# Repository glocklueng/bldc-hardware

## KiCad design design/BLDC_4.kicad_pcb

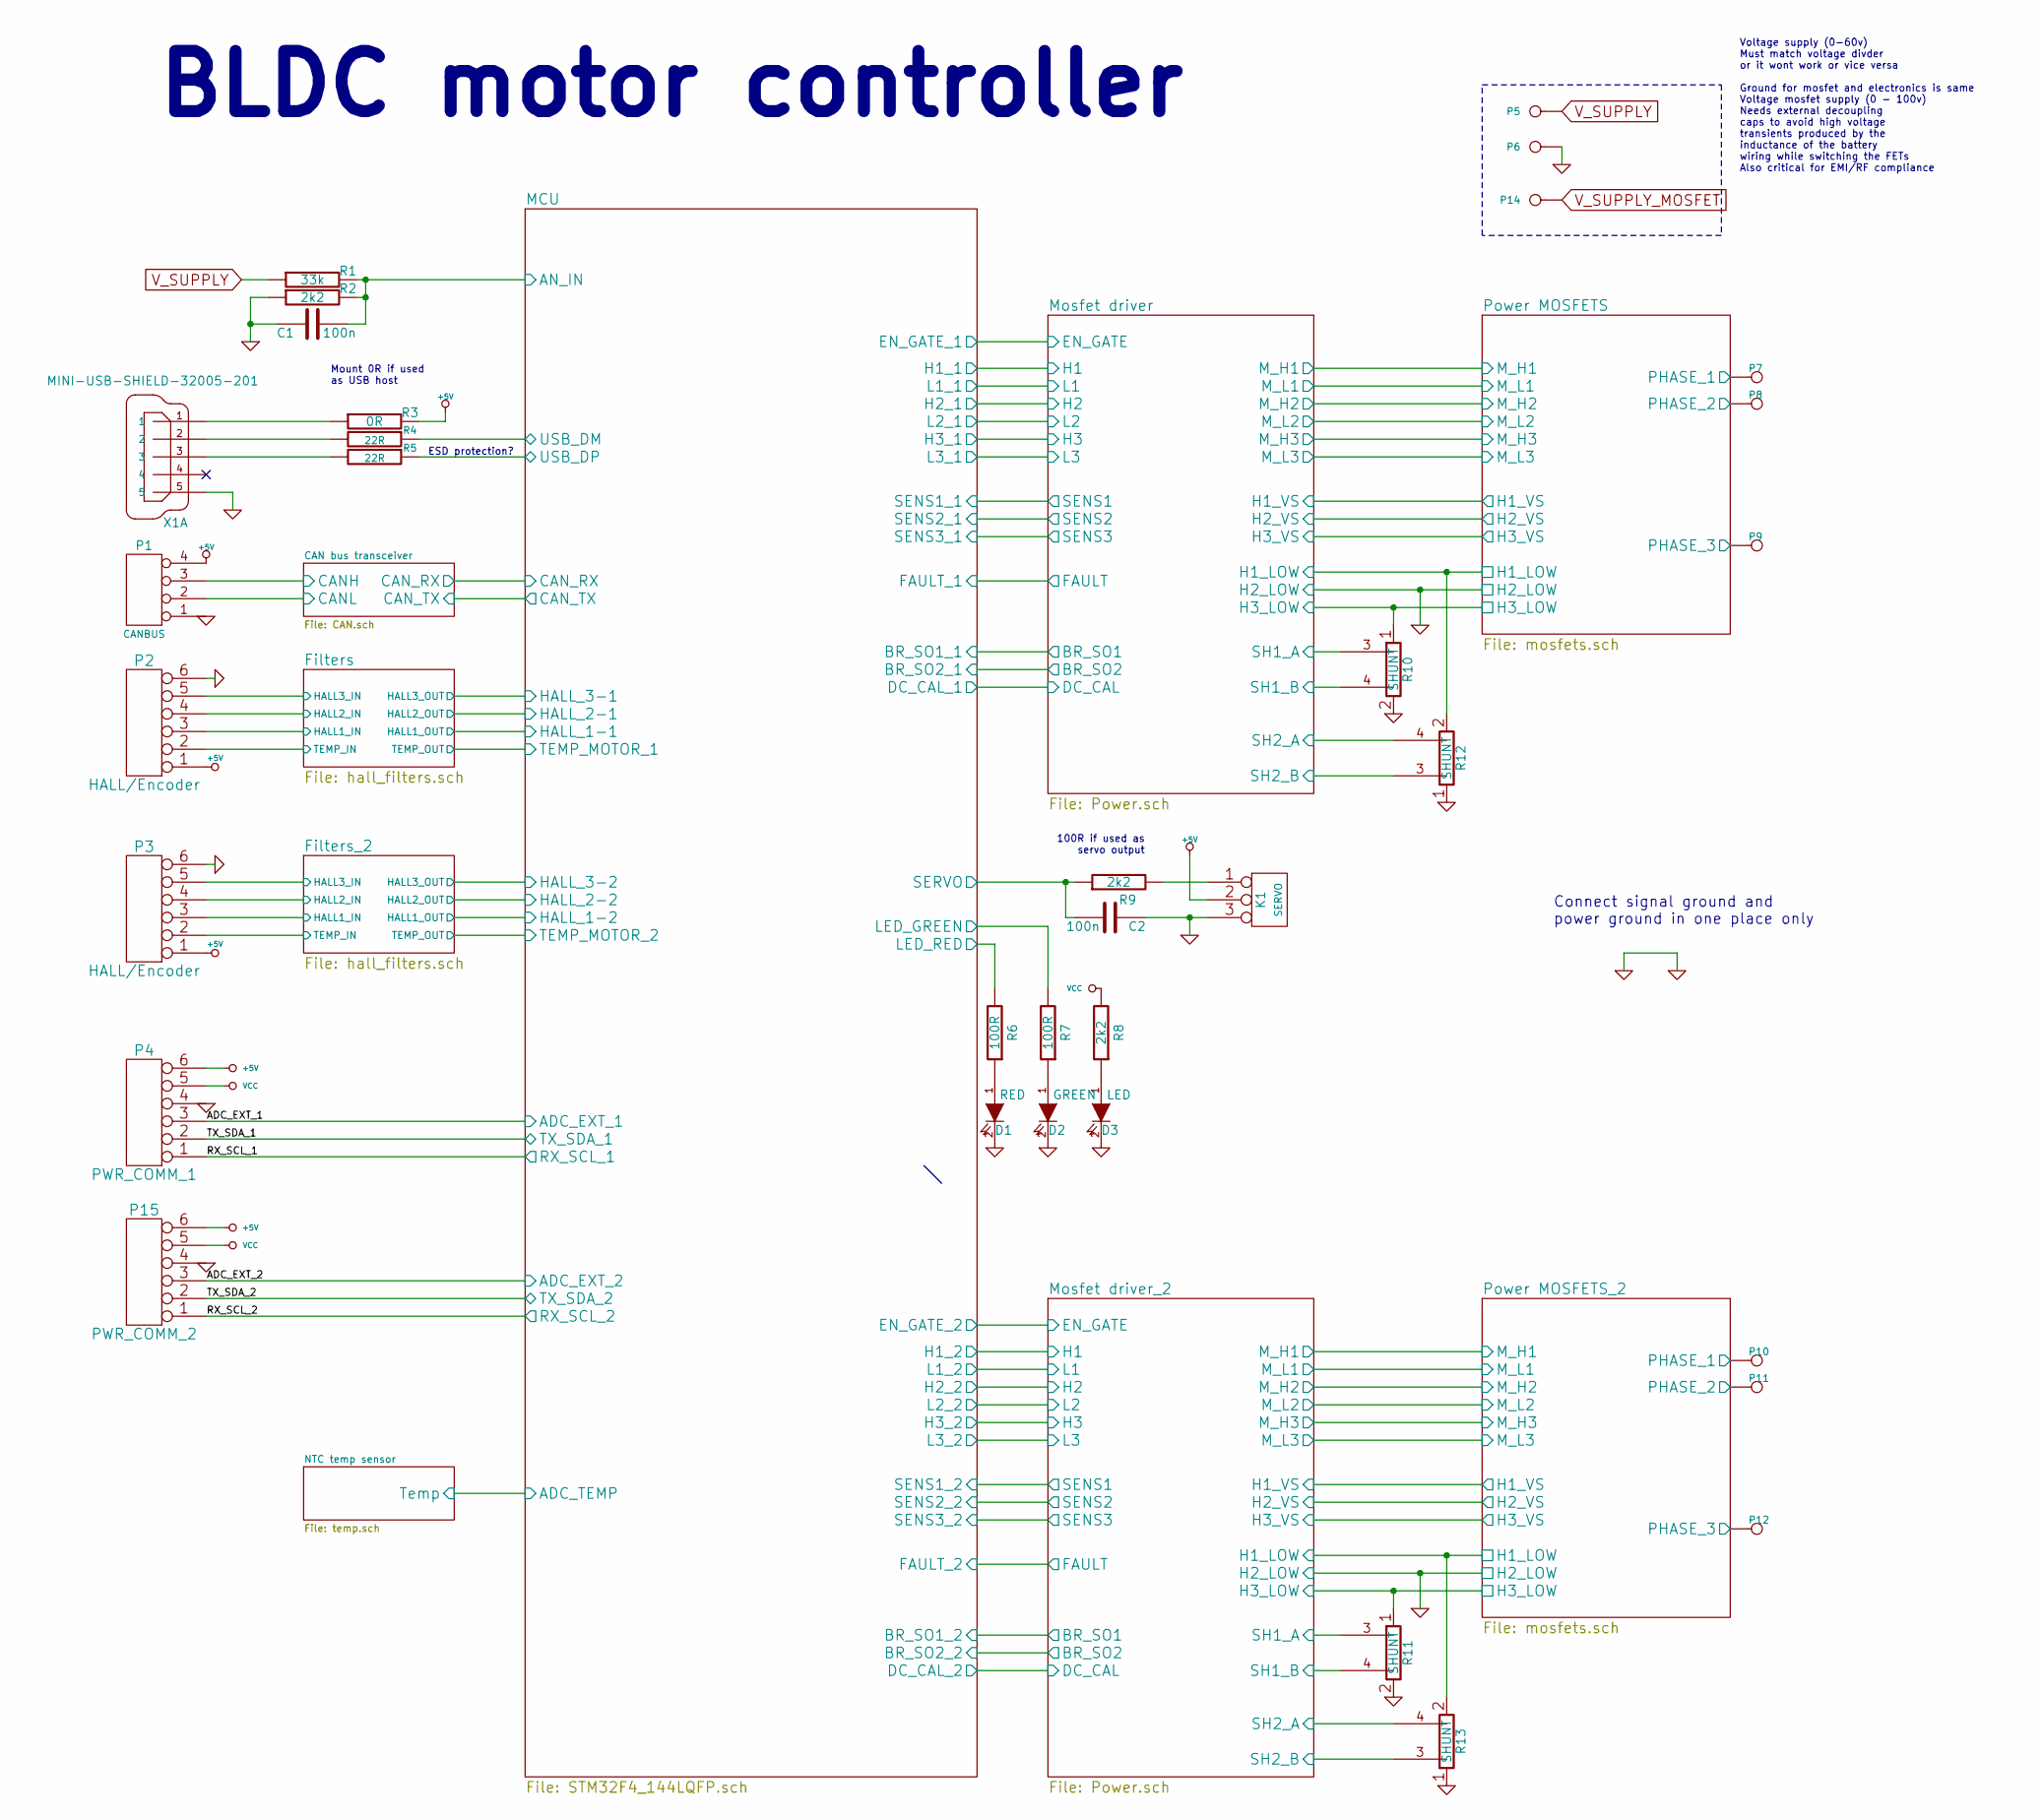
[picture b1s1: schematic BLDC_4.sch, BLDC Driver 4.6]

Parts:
C1, C2: 100n; SMD-0603_c
D1: RED; LED-0603
D2: GREEN; LED-0603
D3: LED; LED-0603
K1: SERVO; pinhead-1X03
P1: CANBUS; pinhead-1X04
P2, P3: HALL/Encoder; MICRO_JST_6
P4: PWR_COMM_1; MICRO_JST_6
P5, P14: IN+; 1PAD_4x5mm
P6: IN-; 1PAD_4x5mm
P7, P10: MOTOR3; 1PAD_4x5mm
P8, P11: MOTOR2; 1PAD_4x5mm
P9, P12: MOTOR1; 1PAD_4x5mm
P15: PWR_COMM_2; MICRO_JST_6
R1: 33k; SMD-0603_r
R2, R8, R9: 2k2; SMD-0603_r
R3: 0R; SMD-0603_r
R4, R5: 22R; SMD-0603_r
R6, R7: 100R; SMD-0603_r
R10, R11, R12, R13: SHUNT; WSLP2726
X1: MINI-USB-SHIELD-32005-201; con-cypressindustries-32005-201

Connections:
+5V: K1.2 (PM), P1.4, P2.1, P3.1, P4.6, P15.6, R3.2; also elsewhere on the board
/CAN bus transceiver/CANH: P1.3; also elsewhere on the board
/CAN bus transceiver/CANL: P1.2; also elsewhere on the board
/Filters/HALL1_IN: P2.3; also elsewhere on the board
/Filters/HALL2_IN: P2.4; also elsewhere on the board
/Filters/HALL3_IN: P2.5; also elsewhere on the board
/Filters/TEMP_IN: P2.2; also elsewhere on the board
/Filters_2/HALL1_IN: P3.3; also elsewhere on the board
/Filters_2/HALL2_IN: P3.4; also elsewhere on the board
/Filters_2/HALL3_IN: P3.5; also elsewhere on the board
/Filters_2/TEMP_IN: P3.2; also elsewhere on the board
/MCU/ADC_EXT_1: P4.3; also elsewhere on the board
/MCU/ADC_EXT_2: P15.3; also elsewhere on the board
/MCU/AN_IN: C1.2, R1.2, R2.2; also elsewhere on the board
/MCU/LED_GREEN: R7.2; also elsewhere on the board
/MCU/LED_RED: R6.2; also elsewhere on the board
/MCU/RX_SCL_1: P4.1; also elsewhere on the board
/MCU/RX_SCL_2: P15.1; also elsewhere on the board
/MCU/SERVO: C2.2, R9.1; also elsewhere on the board
/MCU/TX_SDA_1: P4.2; also elsewhere on the board
/MCU/TX_SDA_2: P15.2; also elsewhere on the board
/MCU/USB_DM: R4.1; also elsewhere on the board
/MCU/USB_DP: R5.1; also elsewhere on the board
/Mosfet driver/H3_VS: P9.1; also elsewhere on the board
/Mosfet driver/SH1_A: R10.3; also elsewhere on the board
/Mosfet driver/SH1_B: R10.4; also elsewhere on the board
/Mosfet driver/SH2_A: R12.4; also elsewhere on the board
/Mosfet driver/SH2_B: R12.3; also elsewhere on the board
/Mosfet driver_2/H3_VS: P12.1; also elsewhere on the board
/Mosfet driver_2/SH1_A: R11.3; also elsewhere on the board
/Mosfet driver_2/SH1_B: R11.4; also elsewhere on the board
/Mosfet driver_2/SH2_A: R13.4; also elsewhere on the board
/Mosfet driver_2/SH2_B: R13.3; also elsewhere on the board
GND: C1.1, C2.1, D1.2 (K), D2.2 (K), D3.2 (K), K1.3, P1.1, P2.6, P3.6, P4.4, P6.1, P15.4, R2.1, R10.2, R11.2, R12.1, R13.1, X1.5; also elsewhere on the board
unnamed: D1.1 (A), R6.1
unnamed: D2.1 (A), R7.1
unnamed: D3.1 (A), R8.1
unnamed: K1.1, R9.2
unnamed: R3.1, X1.1
unnamed: R4.2, X1.2
unnamed: R5.2, X1.3
VCC: P4.5, P15.5, R8.2; also elsewhere on the board
V_SUPPLY: P5.1, R1.1; also elsewhere on the board
V_SUPPLY_MOSFET: P14.1; also elsewhere on the board

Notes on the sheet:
100R if used as servo output
Mount 0R if used as USB host
ESD protection?
BLDC motor controller
Voltage mosfet supply (0 - 100v) Needs external decoupling caps to avoid high voltage transients produced by the inductance of the battery wiring while switching the FETs Also critical for EMI/RF compliance
Connect signal ground and power ground in one place only
Voltage supply (0-60v) Must match voltage divder or it wont work or vice versa Ground for mosfet and electronics is same

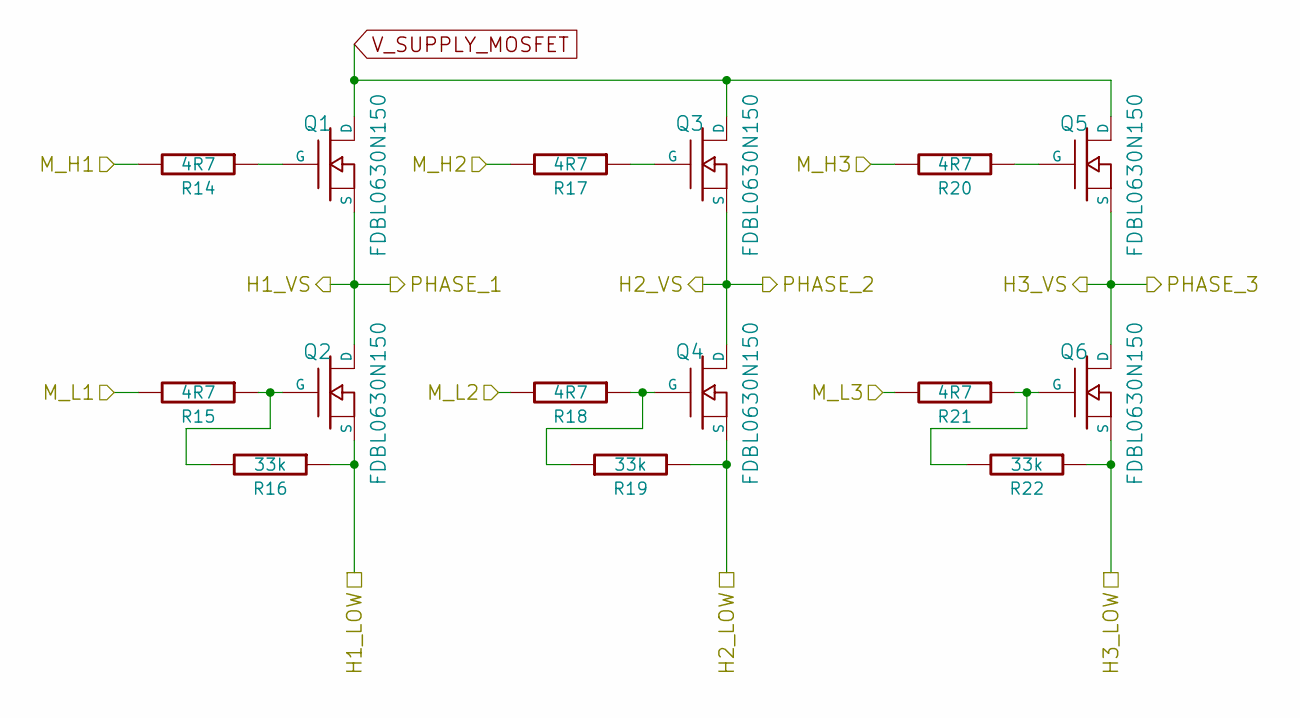
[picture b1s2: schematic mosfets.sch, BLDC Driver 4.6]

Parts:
Q2, Q3, Q5, Q6, Q7, Q10: FDBL0630N150; H-PSOF-8L
R59, R60, R62, R63, R65, R66: 4R7; SMD-0603_r
R61, R64, R67: 33k; SMD-0603_r

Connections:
/Mosfet driver/H3_VS: Q5.S, Q6.D; also elsewhere on the board
/Mosfet driver_2/M_H1: R59.2; also elsewhere on the board
/Mosfet driver_2/M_H2: R62.2; also elsewhere on the board
/Mosfet driver_2/M_H3: R65.2; also elsewhere on the board
/Mosfet driver_2/M_L1: R60.2; also elsewhere on the board
/Mosfet driver_2/M_L2: R63.2; also elsewhere on the board
/Mosfet driver_2/M_L3: R66.2; also elsewhere on the board
GND: Q10.S, R64.2; also elsewhere on the board
unnamed: Q7.G, R59.1
unnamed: Q10.G, R63.1, R64.1
V_SUPPLY_MOSFET: Q3.D, Q5.D, Q7.D; also elsewhere on the board

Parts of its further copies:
Q1, Q4, Q8, Q9, Q11, Q12: FDBL0630N150; H-PSOF-8L
R14, R15, R17, R18, R20, R21: 4R7; SMD-0603_r
R16, R19, R22: 33k; SMD-0603_r

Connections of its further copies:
/Mosfet driver/M_H1: R14.2; also elsewhere on the board
/Mosfet driver/M_H2: R17.2; also elsewhere on the board
/Mosfet driver/M_H3: R20.2; also elsewhere on the board
/Mosfet driver/M_L1: R15.2; also elsewhere on the board
/Mosfet driver/M_L2: R18.2; also elsewhere on the board
/Mosfet driver/M_L3: R21.2; also elsewhere on the board
/Mosfet driver_2/H3_VS: Q11.S, Q12.D; also elsewhere on the board
GND: Q4.S, R19.2; also elsewhere on the board
unnamed: Q1.G, R14.1
unnamed: Q4.G, R18.1, R19.1
V_SUPPLY_MOSFET: Q1.D, Q9.D, Q11.D; also elsewhere on the board

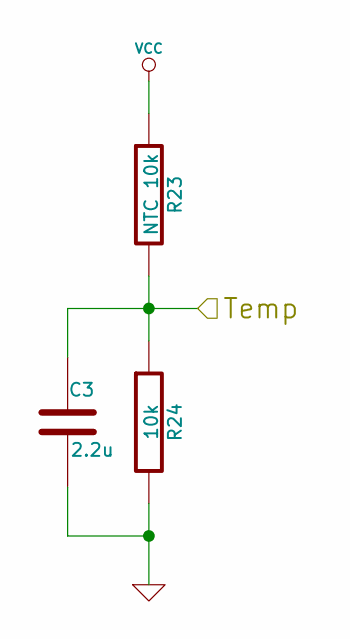
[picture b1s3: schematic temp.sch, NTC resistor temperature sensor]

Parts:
C3: 2.2u; SMD-0603_c
R23: NTC 10k; SMD-0603_r
R24: 10k; SMD-0603_r

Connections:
/MCU/ADC_TEMP: C3.1, R23.2, R24.1; also elsewhere on the board
GND: C3.2, R24.2; also elsewhere on the board
VCC: R23.1; also elsewhere on the board

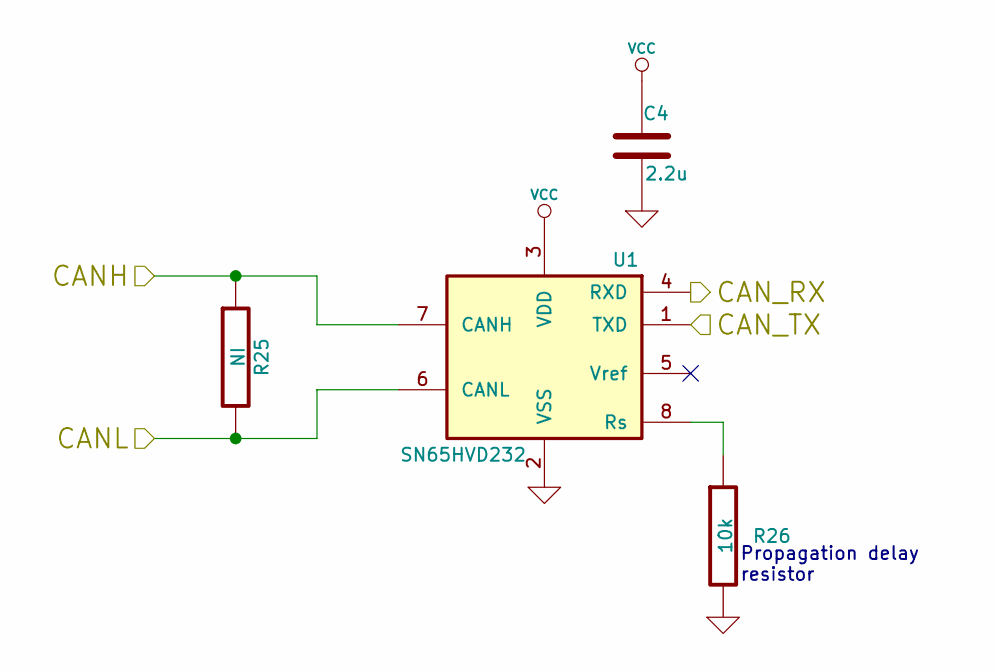
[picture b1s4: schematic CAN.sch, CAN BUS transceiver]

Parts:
C4: 2.2u; SMD-0402
R25: NI; SMD-0603_r
R26: 10k; SMD-0603_r
U1: SN65HVD232; SOIC-8-W

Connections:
/CAN bus transceiver/CANH: R25.1, U1.7 (CANH); also elsewhere on the board
/CAN bus transceiver/CANL: R25.2, U1.6 (CANL); also elsewhere on the board
/CAN bus transceiver/CAN_RX: U1.4 (RXD); also elsewhere on the board
/CAN bus transceiver/CAN_TX: U1.1 (TXD); also elsewhere on the board
GND: C4.2, R26.2, U1.2 (VSS); also elsewhere on the board
unnamed: R26.1, U1.8 (Rs)
VCC: C4.1, U1.3 (VDD); also elsewhere on the board

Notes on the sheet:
Propagation delay resistor

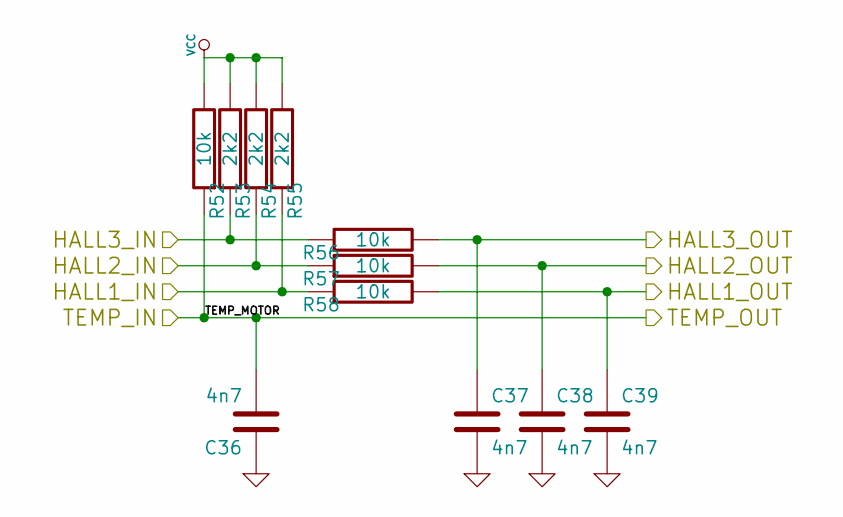
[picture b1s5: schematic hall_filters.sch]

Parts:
C5, C6, C7, C8: 4n7; SMD-0603_c
R27, R31, R32, R33: 10k; SMD-0603_r
R28, R29, R30: 2k2; SMD-0603_r

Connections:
/Filters/HALL1_IN: R30.1, R33.1; also elsewhere on the board
/Filters/HALL1_OUT: C8.1, R33.2; also elsewhere on the board
/Filters/HALL2_IN: R29.1, R32.1; also elsewhere on the board
/Filters/HALL2_OUT: C7.1, R32.2; also elsewhere on the board
/Filters/HALL3_IN: R28.1, R31.1; also elsewhere on the board
/Filters/HALL3_OUT: C6.1, R31.2; also elsewhere on the board
/Filters/TEMP_IN: C5.2, R27.1; also elsewhere on the board
GND: C5.1, C6.2, C7.2, C8.2; also elsewhere on the board
VCC: R27.2, R28.2, R29.2, R30.2; also elsewhere on the board

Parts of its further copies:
C36, C37, C38, C39: 4n7; SMD-0603_c
R52, R56, R57, R58: 10k; SMD-0603_r
R53, R54, R55: 2k2; SMD-0603_r

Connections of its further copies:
/Filters_2/HALL1_IN: R55.1, R58.1; also elsewhere on the board
/Filters_2/HALL1_OUT: C39.1, R58.2; also elsewhere on the board
/Filters_2/HALL2_IN: R54.1, R57.1; also elsewhere on the board
/Filters_2/HALL2_OUT: C38.1, R57.2; also elsewhere on the board
/Filters_2/HALL3_IN: R53.1, R56.1; also elsewhere on the board
/Filters_2/HALL3_OUT: C37.1, R56.2; also elsewhere on the board
/Filters_2/TEMP_IN: C36.2, R52.1; also elsewhere on the board
GND: C36.1, C37.2, C38.2, C39.2; also elsewhere on the board
VCC: R52.2, R53.2, R54.2, R55.2; also elsewhere on the board

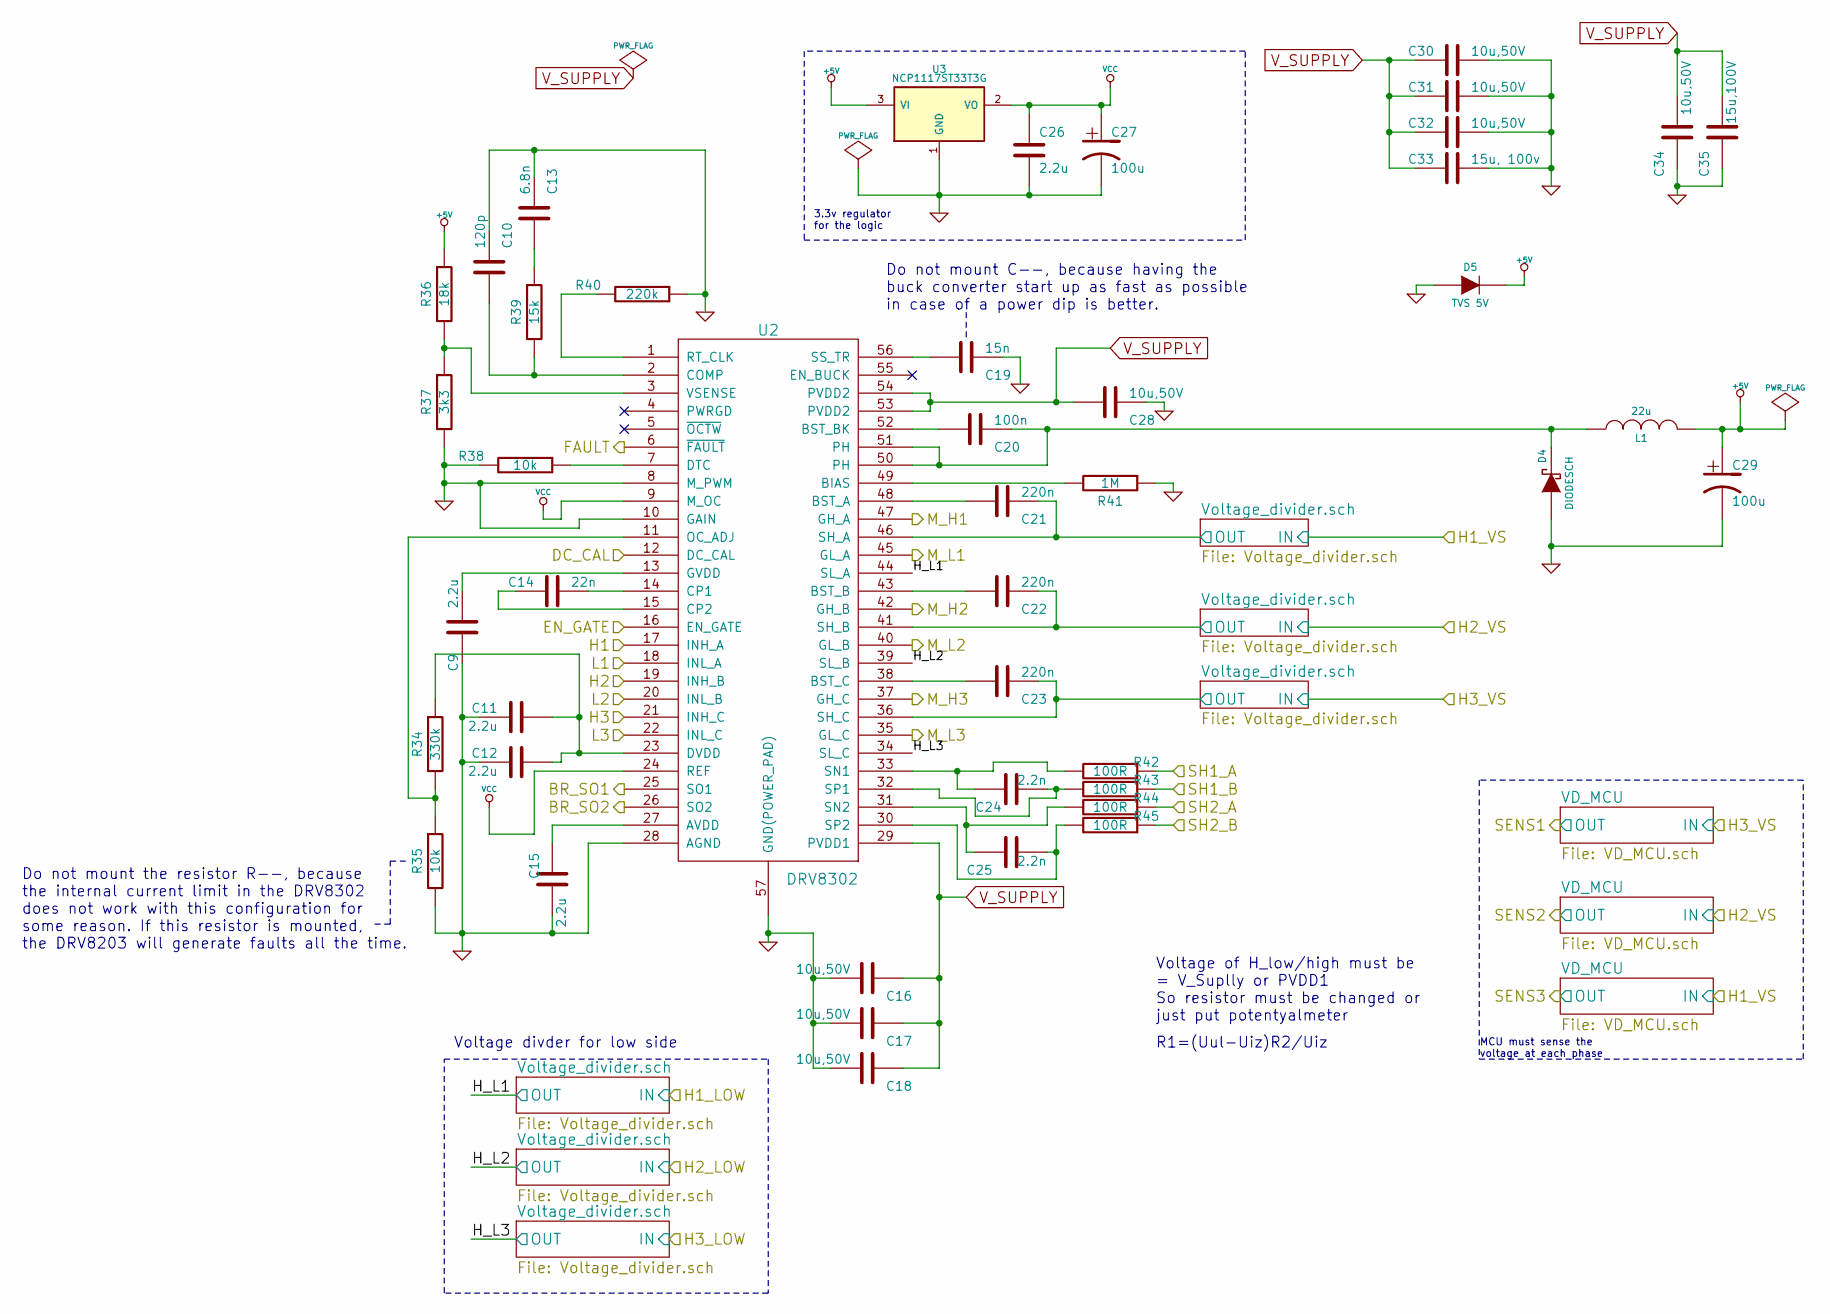
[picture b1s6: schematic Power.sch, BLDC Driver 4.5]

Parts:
C9, C15: 2.2u; SMD-0805
C10: 120p; SMD-0603_c
C11, C12, C26: 2.2u; SMD-0603_c
C13: 6.8n; SMD-0603_c
C14: 22n; SMD-0603_c
C16, C17, C18, C28, C30, C31, C32, C34: 10u,50V; SMD-1206
C19: 15n; SMD-0603_c
C20: 100n; SMD-0603_c
C21, C22, C23: 220n; SMD-0805
C24, C25: 2.2n; SMD-0603_c
C27, C29: 100u; c_tant_B
C33: 15u, 100v; c_2220
C35: 15u,100V; c_2220
D4: DIODESCH; Diode-SMA_Handsoldering
D5: TVS 5V; do214ac
L1: 22u; inductor_smd_8x5mm
R34: 330k; SMD-0603_r
R35, R38: 10k; SMD-0603_r
R36: 18k; SMD-0603_r
R37: 3k3; SMD-0603_r
R39: 15k; SMD-0603_r
R40: 220k; SMD-0603_r
R41: 1M; SMD-0603_r
R42, R43, R44, R45: 100R; SMD-0603_r
U2: DRV8302; TSSOP-56-PP
U3: NCP1117ST33T3G; SOT-223

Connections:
+5V: C29.1, D5.2 (K), L1.2, R36.1, U3.3 (VI); also elsewhere on the board
/Mosfet driver/BR_SO1: U2.25 (SO1); also elsewhere on the board
/Mosfet driver/BR_SO2: U2.26 (SO2); also elsewhere on the board
/Mosfet driver/DC_CAL: U2.12 (DC_CAL); also elsewhere on the board
/Mosfet driver/EN_GATE: U2.16 (EN_GATE); also elsewhere on the board
/Mosfet driver/FAULT: U2.6 (~FAULT); also elsewhere on the board
/Mosfet driver/H1: U2.17 (INH_A); also elsewhere on the board
/Mosfet driver/H2: U2.19 (INH_B); also elsewhere on the board
/Mosfet driver/H3: U2.21 (INH_C); also elsewhere on the board
/Mosfet driver/L1: U2.18 (INL_A); also elsewhere on the board
/Mosfet driver/L2: U2.20 (INL_B); also elsewhere on the board
/Mosfet driver/L3: U2.22 (INL_C); also elsewhere on the board
/Mosfet driver/M_H1: U2.47 (GH_A); also elsewhere on the board
/Mosfet driver/M_H2: U2.42 (GH_B); also elsewhere on the board
/Mosfet driver/M_H3: U2.37 (GH_C); also elsewhere on the board
/Mosfet driver/M_L1: U2.45 (GL_A); also elsewhere on the board
/Mosfet driver/M_L2: U2.40 (GL_B); also elsewhere on the board
/Mosfet driver/M_L3: U2.35 (GL_C); also elsewhere on the board
/Mosfet driver/SH1_A: R42.1; also elsewhere on the board
/Mosfet driver/SH1_B: R43.1; also elsewhere on the board
/Mosfet driver/SH2_A: R44.1; also elsewhere on the board
/Mosfet driver/SH2_B: R45.1; also elsewhere on the board
/Mosfet driver/Voltage_divider.sch/OUT: C21.1, C22.1, C23.1, U2.34 (SL_C), U2.36 (SH_C), U2.39 (SL_B), U2.41 (SH_B), U2.44 (SL_A), U2.46 (SH_A); also elsewhere on the board
GND: C9.2, C10.1, C11.1, C12.1, C13.1, C15.1, C16.2, C17.2, C18.2, C19.1, C26.2, C27.2, C28.1, C29.2, C30.1, C31.1, C32.1, C33.1, C34.1, C35.1, D4.1 (A), D5.1 (A), R35.2, R37.2, R38.2, R40.1, R41.1, U2.8 (M_PWM), U2.10 (GAIN), U2.28 (AGND), U2.57 (GND(POWER_PAD)), U3.1 (GND); also elsewhere on the board
unnamed: C9.1, U2.13 (GVDD)
unnamed: C10.2, R39.2, U2.2 (COMP)
unnamed: C11.2, C12.2, R34.1, U2.23 (DVDD)
unnamed: C13.2, R39.1
unnamed: C14.1, U2.14 (CP1)
unnamed: C14.2, U2.15 (CP2)
unnamed: C15.2, U2.27 (AVDD)
unnamed: C19.2, U2.56 (SS_TR)
unnamed: C20.1, D4.2 (K), L1.1, U2.50 (PH), U2.51 (PH)
unnamed: C20.2, U2.52 (BST_BK)
unnamed: C21.2, U2.48 (BST_A)
unnamed: C22.2, U2.43 (BST_B)
unnamed: C23.2, U2.38 (BST_C)
unnamed: C24.1, R42.2, U2.33 (SN1)
unnamed: C24.2, R43.2, U2.32 (SP1)
unnamed: C25.1, R44.2, U2.31 (SN2)
unnamed: C25.2, R45.2, U2.30 (SP2)
unnamed: R34.2, R35.1, U2.11 (OC_ADJ)
unnamed: R36.2, R37.1, U2.3 (VSENSE)
unnamed: R38.1, U2.7 (DTC)
unnamed: R40.2, U2.1 (RT_CLK)
unnamed: R41.2, U2.49 (BIAS)
VCC: C26.1, C27.1, U2.9 (M_OC), U2.24 (REF), U3.2 (VO); also elsewhere on the board
V_SUPPLY: C16.1, C17.1, C18.1, C28.2, C30.2, C31.2, C32.2, C33.2, C34.2, C35.2, U2.29 (PVDD1), U2.53 (PVDD2), U2.54 (PVDD2); also elsewhere on the board

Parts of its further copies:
C52, C58: 2.2u; SMD-0805
C53: 120p; SMD-0603_c
C54, C55, C69: 2.2u; SMD-0603_c
C56: 6.8n; SMD-0603_c
C57: 22n; SMD-0603_c
C59, C60, C61, C71, C73, C74, C75, C77: 10u,50V; SMD-1206
C62: 15n; SMD-0603_c
C63: 100n; SMD-0603_c
C64, C65, C66: 220n; SMD-0805
C67, C68: 2.2n; SMD-0603_c
C70, C72: 100u; c_tant_B
C76: 15u, 100v; c_2220
C78: 15u,100V; c_2220
D6: DIODESCH; Diode-SMA_Handsoldering
D7: TVS 5V; do214ac
L2: 22u; inductor_smd_8x5mm
R68: 330k; SMD-0603_r
R69, R72: 10k; SMD-0603_r
R70: 18k; SMD-0603_r
R71: 3k3; SMD-0603_r
R73: 15k; SMD-0603_r
R74: 220k; SMD-0603_r
R75: 1M; SMD-0603_r
R76, R77, R78, R79: 100R; SMD-0603_r
U5: DRV8302; TSSOP-56-PP
U6: NCP1117ST33T3G; SOT-223

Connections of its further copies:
+5V: C72.1, D7.2 (K), L2.2, R70.1, U6.3 (VI); also elsewhere on the board
/Mosfet driver_2/BR_SO1: U5.25 (SO1); also elsewhere on the board
/Mosfet driver_2/BR_SO2: U5.26 (SO2); also elsewhere on the board
/Mosfet driver_2/DC_CAL: U5.12 (DC_CAL); also elsewhere on the board
/Mosfet driver_2/EN_GATE: U5.16 (EN_GATE); also elsewhere on the board
/Mosfet driver_2/FAULT: U5.6 (~FAULT); also elsewhere on the board
/Mosfet driver_2/H1: U5.17 (INH_A); also elsewhere on the board
/Mosfet driver_2/H2: U5.19 (INH_B); also elsewhere on the board
/Mosfet driver_2/H3: U5.21 (INH_C); also elsewhere on the board
/Mosfet driver_2/L1: U5.18 (INL_A); also elsewhere on the board
/Mosfet driver_2/L2: U5.20 (INL_B); also elsewhere on the board
/Mosfet driver_2/L3: U5.22 (INL_C); also elsewhere on the board
/Mosfet driver_2/M_H1: U5.47 (GH_A); also elsewhere on the board
/Mosfet driver_2/M_H2: U5.42 (GH_B); also elsewhere on the board
/Mosfet driver_2/M_H3: U5.37 (GH_C); also elsewhere on the board
/Mosfet driver_2/M_L1: U5.45 (GL_A); also elsewhere on the board
/Mosfet driver_2/M_L2: U5.40 (GL_B); also elsewhere on the board
/Mosfet driver_2/M_L3: U5.35 (GL_C); also elsewhere on the board
/Mosfet driver_2/SH1_A: R76.1; also elsewhere on the board
/Mosfet driver_2/SH1_B: R77.1; also elsewhere on the board
/Mosfet driver_2/SH2_A: R78.1; also elsewhere on the board
/Mosfet driver_2/SH2_B: R79.1; also elsewhere on the board
/Mosfet driver_2/Voltage_divider.sch/OUT: C64.1, C65.1, C66.1, U5.34 (SL_C), U5.36 (SH_C), U5.39 (SL_B), U5.41 (SH_B), U5.44 (SL_A), U5.46 (SH_A); also elsewhere on the board
GND: C52.2, C53.1, C54.1, C55.1, C56.1, C58.1, C59.2, C60.2, C61.2, C62.1, C69.2, C70.2, C71.1, C72.2, C73.1, C74.1, C75.1, C76.1, C77.1, C78.1, D6.1 (A), D7.1 (A), R69.2, R71.2, R72.2, R74.1, R75.1, U5.8 (M_PWM), U5.10 (GAIN), U5.28 (AGND), U5.57 (GND(POWER_PAD)), U6.1 (GND); also elsewhere on the board
unnamed: C52.1, U5.13 (GVDD)
unnamed: C53.2, R73.2, U5.2 (COMP)
unnamed: C54.2, C55.2, R68.1, U5.23 (DVDD)
unnamed: C56.2, R73.1
unnamed: C57.1, U5.14 (CP1)
unnamed: C57.2, U5.15 (CP2)
unnamed: C58.2, U5.27 (AVDD)
unnamed: C62.2, U5.56 (SS_TR)
unnamed: C63.1, D6.2 (K), L2.1, U5.50 (PH), U5.51 (PH)
unnamed: C63.2, U5.52 (BST_BK)
unnamed: C64.2, U5.48 (BST_A)
unnamed: C65.2, U5.43 (BST_B)
unnamed: C66.2, U5.38 (BST_C)
unnamed: C67.1, R76.2, U5.33 (SN1)
unnamed: C67.2, R77.2, U5.32 (SP1)
unnamed: C68.1, R78.2, U5.31 (SN2)
unnamed: C68.2, R79.2, U5.30 (SP2)
unnamed: R68.2, R69.1, U5.11 (OC_ADJ)
unnamed: R70.2, R71.1, U5.3 (VSENSE)
unnamed: R72.1, U5.7 (DTC)
unnamed: R74.2, U5.1 (RT_CLK)
unnamed: R75.2, U5.49 (BIAS)
VCC: C69.1, C70.1, U5.9 (M_OC), U5.24 (REF), U6.2 (VO); also elsewhere on the board
V_SUPPLY: C59.1, C60.1, C61.1, C71.2, C73.2, C74.2, C75.2, C76.2, C77.2, C78.2, U5.29 (PVDD1), U5.53 (PVDD2), U5.54 (PVDD2); also elsewhere on the board

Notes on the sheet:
MCU must sense the voltage at each phase
3.3v regulator for the logic
Do not mount the resistor R--, because the internal current limit in the DRV8302 does not work with this configuration for some reason. If this resistor is mounted, the DRV8203 will generate faults all the time.
Do not mount C--, because having the buck converter start up as fast as possible in case of a power dip is better.
Voltage of H_low/high must be = V_Suplly or PVDD1 So resistor must be changed or just put potentyalmeter
Voltage divder for low side
R1=(Uul-Uiz)R2/Uiz
